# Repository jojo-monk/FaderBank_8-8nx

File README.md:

# 8+8nx Faderbank

A modular faderbank based on the [16nx](https://github.com/16n-faderbank/16nx) project, designed for Eurorack synthesizers and DAW MIDI control. Sends MIDI data and CV signals.

---

## What is it?

The 8+8nx is a DIY faderbank that splits the original 16nx design into two separate PCBs, making it more flexible and easier to build in different configurations.

It is designed for musicians who want hands-on control over their Eurorack setup or DAW, with a compact and modular form factor.

---

## Differences from the 16nx

| Feature | 16nx | 8+8nx |
|---|---|---|
| PCB | Single board | 2 PCBs (ControlBoard + MainBoard) |
| Faders | 16 | 8 per ControlBoard (expandable to 16) |
| MCU | RP2040 chip | Raspberry Pi Pico |
| Mute switches | No | Yes, per fader |
| I2C port | Yes | Removed |
| GPIO exposure | Partial | All free Pico pins exposed |

---

## Hardware

- **MainBoard** — hosts the Raspberry Pi Pico, handles USB MIDI, CV outputs and all connections
- **ControlBoard** — hosts 8 faders and mute switches, connects to the MainBoard

You can run a single ControlBoard (8 faders) or chain two for a full 16-fader setup.

---

## Features

- USB MIDI output
- CV output
- 8 or 16 fader configuration
- Mute switch per fader
- All free GPIO pins of the Raspberry Pi Pico exposed for customization
- Compatible with Eurorack synthesizers and DAWs

---

## Firmware

Based on the 16nx firmware, adapted for the Raspberry Pi Pico.

### Build requirements

- [Raspberry Pi Pico SDK](https://github.com/raspberrypi/pico-sdk)
- CMake 3.13+
- ARM GCC toolchain

### Build

```bash
git clone https://github.com/jojo-monk/8-8nx.git
cd 8-8nx/firmware
mkdir build && cd build
cmake ..
make
```

Flash the resulting `.uf2` file onto your Pico by holding BOOTSEL while plugging it in, then drag and drop the file.

---

## Project status

✅ Tested and working

---

## Credits

Based on the [16nx faderbank](https://github.com/16n-faderbank/16nx) project.

---

## License

Hardware and firmware released under the same license as the original 16nx project.

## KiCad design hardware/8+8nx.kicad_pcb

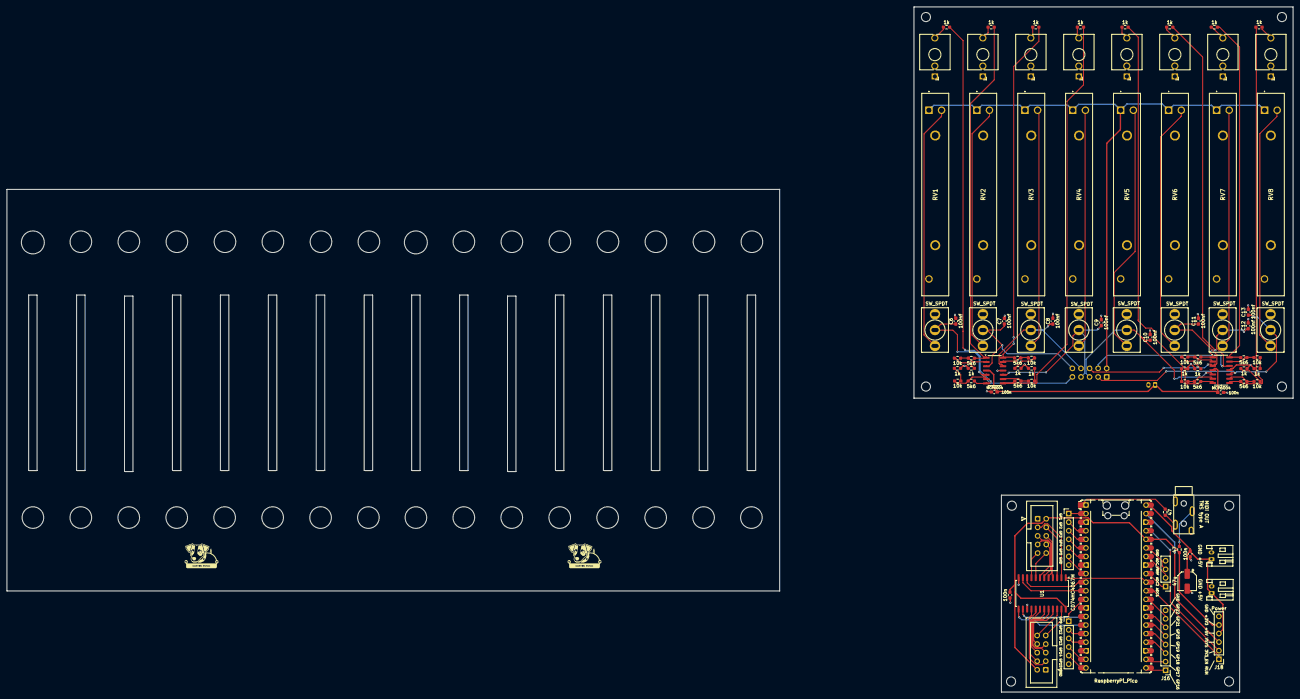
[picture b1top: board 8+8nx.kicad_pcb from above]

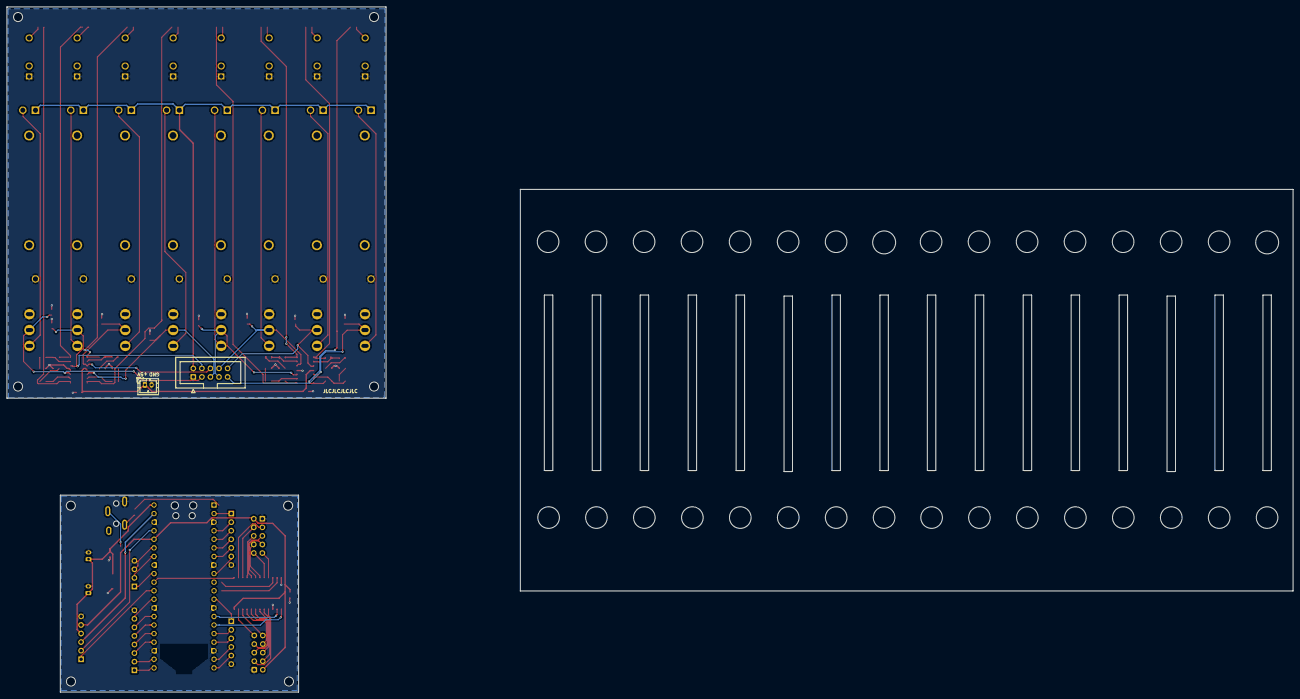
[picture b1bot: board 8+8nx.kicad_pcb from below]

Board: 2 copper layers, 112.4 x 116.0 mm, 95 parts (2 on the bottom side), 91 nets.

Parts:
A1: RaspberryPi_Pico; RaspberryPi_Pico_Common_Unspecified
C1, C3, C4, C5: 100n; C_0603_1608Metric_Pad1.08x0.95mm_HandSolder
C2: 47u; CP_Elec_5x5.4
C6, C7, C8, C9, C10, C11, C12, C13: 100nf; C_0603_1608Metric_Pad1.08x0.95mm_HandSolder
H1, H2, H3, H4, H5, H6, H7, H8: MountingHole; MountingHole_2.7mm_M2.5
J1: AudioJack3_SwitchT; Schurter 4832.2330
J2: Conn_01x02_Pin; JST_PH_S2B-PH-K_1x02_P2.00mm_Horizontal
J3, J4: Conn_01x10_Socket; IDC-Header_2x05_P2.54mm_Vertical
J5: Conn_01x02_Socket; JST_PH_B2B-PH-K_1x02_P2.00mm_Vertical
J6: Conn_01x10_Pin; IDC-Header_2x05_P2.54mm_Vertical
J7, J8, J9, J10, J11, J12, J13, J14: AudioJack2_SwitchT; AudioJack_3.5mm
J15: Conn_01x02_Socket; JST_PH_S2B-PH-K_1x02_P2.00mm_Horizontal
J16: GPIO16-22; PinHeader_1x08_P2.54mm_Vertical
J17: ADC; PinHeader_1x04_P2.54mm_Vertical
J18: Power; PinHeader_1x06_P2.54mm_Vertical
J19: GPIO1-6; PinHeader_1x07_P2.54mm_Vertical
J20: GPIO9-15; PinHeader_1x06_P2.54mm_Vertical
R1, R2: 47; R_0603_1608Metric_Pad0.98x0.95mm_HandSolder
R3, R4, R9, R10, R15, R16, R21, R22, R27, R28, R29, R30, R31, R32, R33, R34: 1k; R_0603_1608Metric_Pad0.98x0.95mm_HandSolder
R5, R6, R11, R12, R17, R18, R23, R24: 10k; R_0603_1608Metric_Pad0.98x0.95mm_HandSolder
R7, R8, R13, R14, R19, R20, R25, R26: 5k6; R_0603_1608Metric_Pad0.98x0.95mm_HandSolder
RV1, RV2, RV3, RV4, RV5, RV6, RV7, RV8: R_Potentiometer; RS45111A900F
SW1, SW2, SW3, SW4, SW5, SW6, SW7, SW8: SW_SPDT; Switch_Toggle_SPDT_Mini_SolderLug
U1: CD74HC4067M; SOIC-24W_7.5x15.4mm_P1.27mm
U2, U3: MCP6004; SOIC-14_3.9x8.7mm_P1.27mm

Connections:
3V3_EN: A1.37 (3V3_EN), J18.2
+3V3: A1.36 (3V3), C3.1, J3.2, J4.2, J6.2, J18.5, R1.2, RV1.1, RV2.1, RV3.1, RV4.1, RV5.1, RV6.1, RV7.1, RV8.1, U1.24 (VCC)
+5V: A1.40 (VBUS), C1.1, C2.1, C4.1, C5.1, J2.1, J5.1, J15.1, J18.4, U2.4 (V+), U3.4 (V+)
/A_IN: A1.31 (GPIO26_ADC0), U1.1 (COM)
/Faders & Analog Outs/CV0: R8.1, R27.1, U2.7
/Faders & Analog Outs/CV1: R14.1, R28.1, U2.1
/Faders & Analog Outs/CV2: R20.1, R29.1, U2.14
/Faders & Analog Outs/CV3: R26.1, R30.1, U2.8
/Faders & Analog Outs/CV4: R7.1, R31.1, U3.7
/Faders & Analog Outs/CV5: R13.1, R32.1, U3.1
/Faders & Analog Outs/CV6: R19.1, R33.1, U3.14
/Faders & Analog Outs/CV7: R25.1, R34.1, U3.8
/MIDI_OUT: A1.1 (GPIO0), R2.2
/M_3V3: J1.R, R1.1
/M_OUT: J1.T, R2.1
/S0: A1.10 (GPIO7), U1.10 (S0)
/S1: A1.11 (GPIO8), U1.11 (S1)
/S2: A1.14 (GPIO10), U1.14 (S2)
/S3: A1.15 (GPIO11), U1.13 (S3)
ADC1: A1.32 (GPIO27_ADC1), J17.1
ADC2: A1.34 (GPIO28_ADC2), J17.2
ADC_VREF: A1.35 (ADC_VREF), J17.3
GND: A1.3 (GND), A1.8 (GND), A1.13 (GND), A1.18 (GND), A1.23 (GND), A1.28 (GND), A1.38 (GND), C1.2, C2.2, C3.2, C4.2, C5.2, C6.2, C7.2, C8.2, C9.2, C10.2, C11.2, C12.2, C13.2, J1.S, J2.2, J3.1, J4.1, J5.2, J6.1, J7.S, J8.S, J9.S, J10.S, J11.S, J12.S, J13.S, J14.S, J15.2, J16.8, J17.4, J18.6, J19.7, J20.6, R3.2, R4.2, R9.2, R10.2, R15.2, R16.2, R21.2, R22.2, RV1.3, RV2.3, RV3.3, RV4.3, RV5.3, RV6.3, RV7.3, RV8.3, SW1.1 (A), SW2.1 (A), SW3.1 (A), SW4.1 (A), SW5.1 (A), SW6.1 (A), SW7.1 (A), SW8.1 (A), U1.12 (GND), U1.15 (~E), U2.11 (V-), U3.11 (V-)
GPIO01: A1.2 (GPIO1), J19.1
GPIO02: A1.4 (GPIO2), J19.2
GPIO03: A1.5 (GPIO3), J19.3
GPIO04: A1.6 (GPIO4), J19.4
GPIO05: A1.7 (GPIO5), J19.5
GPIO06: A1.9 (GPIO6), J19.6
GPIO09: A1.12 (GPIO9), J20.1
GPIO12: A1.16 (GPIO12), J20.2
GPIO13: A1.17 (GPIO13), J20.3
GPIO14: A1.19 (GPIO14), J20.4
GPIO15: A1.20 (GPIO15), J20.5
GPIO16: A1.21 (GPIO16), J16.1
GPIO17: A1.22 (GPIO17), J16.2
GPIO18: A1.24 (GPIO18), J16.3
GPIO19: A1.25 (GPIO19), J16.4
GPIO20: A1.26 (GPIO20), J16.5
GPIO21: A1.27 (GPIO21), J16.6
GPIO22: A1.29 (GPIO22), J16.7
unnamed: J7.T, R27.2
unnamed: J8.T, R28.2
unnamed: J9.T, R29.2
unnamed: J10.T, R30.2
unnamed: J11.T, R31.2
unnamed: J12.T, R32.2
unnamed: J13.T, R33.2
unnamed: J14.T, R34.2
unnamed: R3.1, R5.2
unnamed: R4.1, R6.2
unnamed: R10.1, R11.2
unnamed: R9.1, R12.2
unnamed: R15.1, R17.2
unnamed: R16.1, R18.2
unnamed: R21.1, R23.2
unnamed: R22.1, R24.2
unnamed: RV1.2, SW1.3 (C)
unnamed: RV2.2, SW2.3 (C)
unnamed: RV3.2, SW3.3 (C)
unnamed: RV4.2, SW4.3 (C)
unnamed: RV5.2, SW5.3 (C)
unnamed: RV6.2, SW6.3 (C)
unnamed: RV7.2, SW7.3 (C)
unnamed: RV8.2, SW8.3 (C)
unnamed: R11.1, R14.2, U2.2 (-)
unnamed: R6.1, R8.2, U2.6 (-)
unnamed: R24.1, R26.2, U2.9 (-)
unnamed: R18.1, R20.2, U2.13 (-)
unnamed: R12.1, R13.2, U3.2 (-)
unnamed: R5.1, R7.2, U3.6 (-)
unnamed: R23.1, R25.2, U3.9 (-)
unnamed: R17.1, R19.2, U3.13 (-)
RUN: A1.30 (RUN), J18.1
VSYS: A1.39 (VSYS), J18.3
W0: C6.1, J3.9, J6.9, SW1.2 (B), U1.9 (I0), U2.5 (+)
W1: C7.1, J3.10, J6.10, SW2.2 (B), U1.8 (I1), U2.3 (+)
W2: C8.1, J3.8, J6.8, SW3.2 (B), U1.7 (I2), U2.12 (+)
W3: C9.1, J3.7, J6.7, SW4.2 (B), U1.6 (I3), U2.10 (+)
W4: C10.1, J3.5, J6.5, SW5.2 (B), U1.5 (I4), U3.5 (+)
W5: C11.1, J3.6, J6.6, SW6.2 (B), U1.4 (I5), U3.3 (+)
W6: C12.1, J3.4, J6.4, SW7.2 (B), U1.3 (I6), U3.12 (+)
W7: C13.1, J3.3, J6.3, SW8.2 (B), U1.2 (I7), U3.10 (+)
W8: J4.9, U1.23 (I8)
W9: J4.10, U1.22 (I9)
W10: J4.8, U1.21 (I10)
W11: J4.7, U1.20 (I11)
W12: J4.5, U1.19 (I12)
W13: J4.6, U1.18 (I13)
W14: J4.4, U1.17 (I14)
W15: J4.3, U1.16 (I15)

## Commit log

2026-03-24 Add Images README and 3D Add README, images and 3D files
